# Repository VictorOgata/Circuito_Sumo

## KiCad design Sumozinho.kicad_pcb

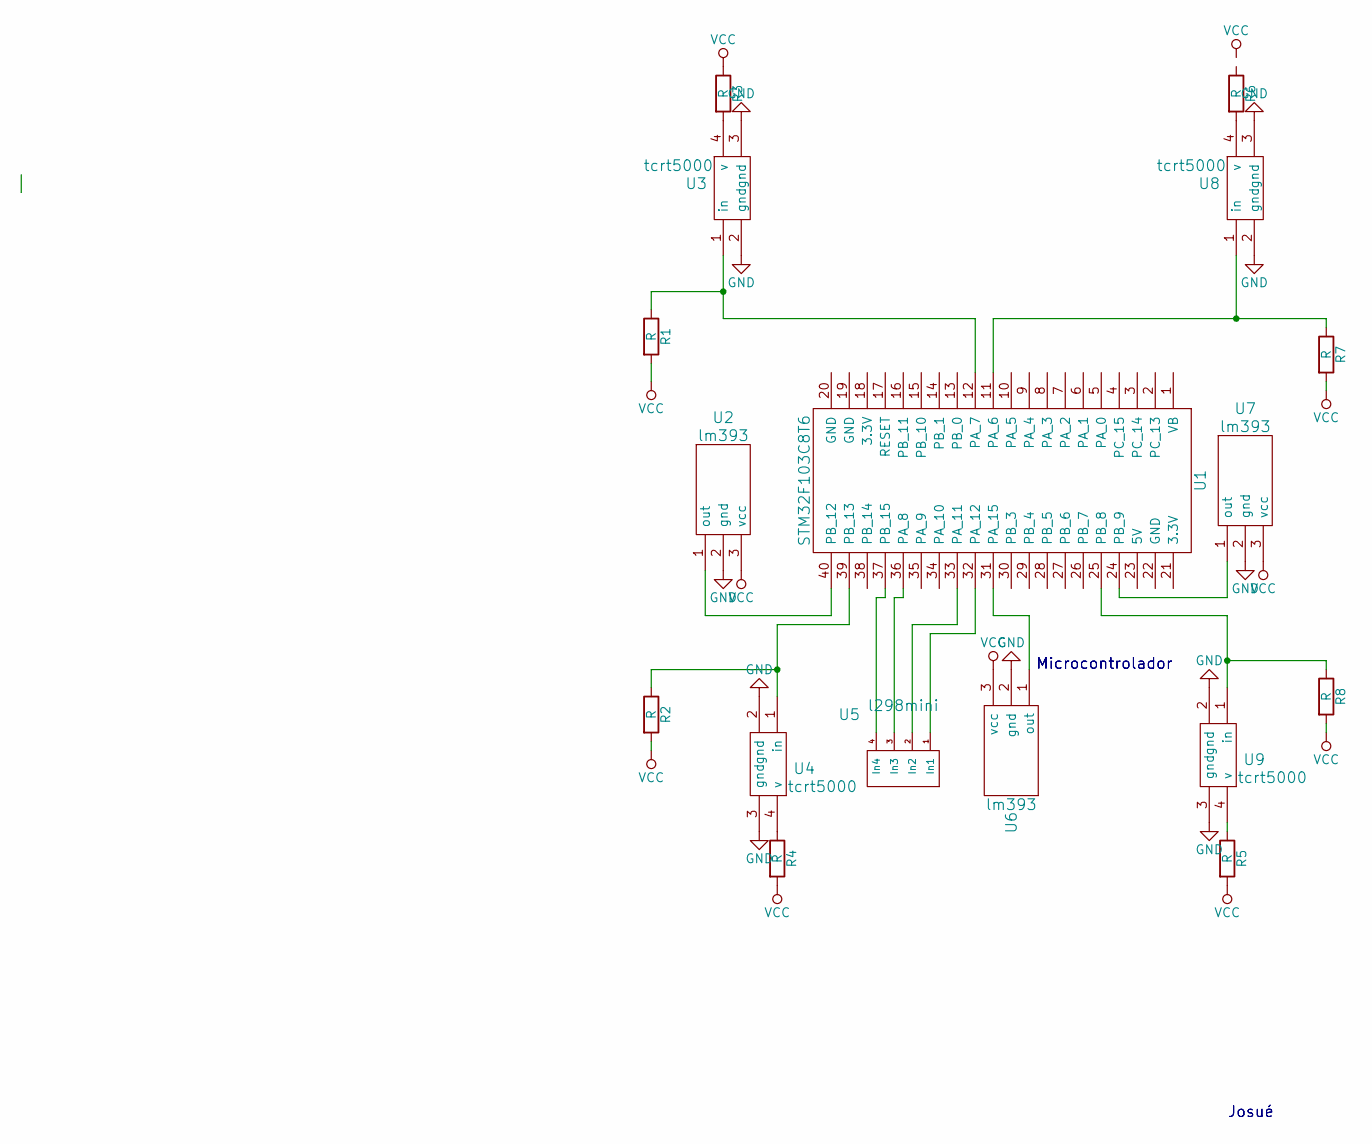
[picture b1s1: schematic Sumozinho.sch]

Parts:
R1, R2, R3, R4, R5, R6, R7, R8: R; R_0805_HandSoldering
U1: STM32F103C8T6; stm32
U2, U6, U7: lm393
U3, U4, U8, U9: tcrt5000
U5: l298mini; l298nmini

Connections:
GND: U2.2 (gnd), U3.2 (gnd), U3.3 (gnd), U4.2 (gnd), U4.3 (gnd), U6.2 (gnd), U7.2 (gnd), U8.2 (gnd), U8.3 (gnd), U9.2 (gnd), U9.3 (gnd)
unnamed: R1.1, U1.12 (PA_7), U3.1 (in)
unnamed: R2.1, U1.39 (PB_13), U4.1 (in)
unnamed: R3.2, U3.4 (v)
unnamed: R4.1, U4.4 (v)
unnamed: R5.1, U9.4 (v)
unnamed: R6.2, U8.4 (v)
unnamed: R7.1, U1.11 (PA_6), U8.1 (in)
unnamed: R8.1, U1.25 (PB_8), U9.1 (in)
unnamed: U1.24 (PB_9), U7.1 (out)
unnamed: U1.31 (PA_15), U6.1 (out)
unnamed: U1.32 (PA_12), U5.1 (In1)
unnamed: U1.33 (PA_11), U5.2 (In2)
unnamed: U1.36 (PA_8), U5.3 (In3)
unnamed: U1.37 (PB_15), U5.4 (In4)
unnamed: U1.40 (PB_12), U2.1 (out)
VCC: R1.2, R2.2, R3.1, R4.2, R5.2, R7.2, R8.2, U2.3 (vcc), U6.3 (vcc), U7.3 (vcc)

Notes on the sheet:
Microcontrolador
Josué

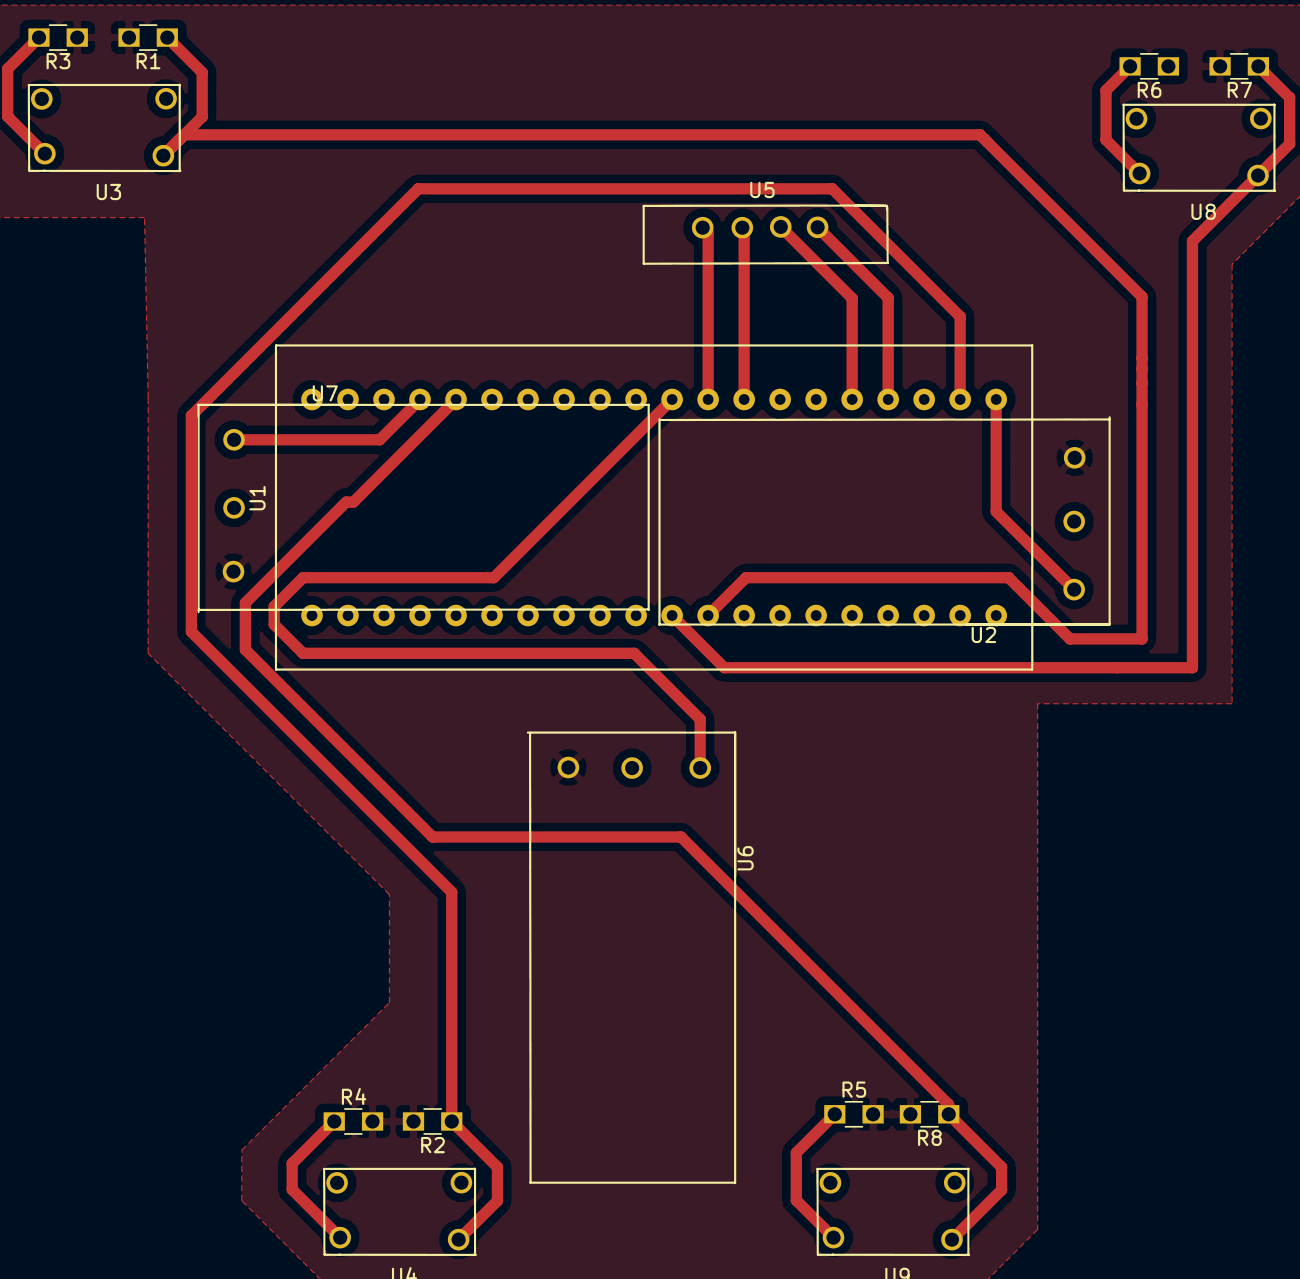
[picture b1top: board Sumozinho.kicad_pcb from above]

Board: 2 copper layers, 17 parts (0 on the bottom side), 17 nets.

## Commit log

2018-09-24 Initial Schematic
2018-09-24 Minor changes
2018-09-26 Adds new footprints
2018-09-26 Ratnest ready
2018-09-30 Auto stash before merge of "master" and "origin/master"
2018-10-05 Hot fixes
